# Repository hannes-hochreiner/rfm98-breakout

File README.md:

# rfm98-breakout
Breakout board for the RFM98 LoRa transceiver module.

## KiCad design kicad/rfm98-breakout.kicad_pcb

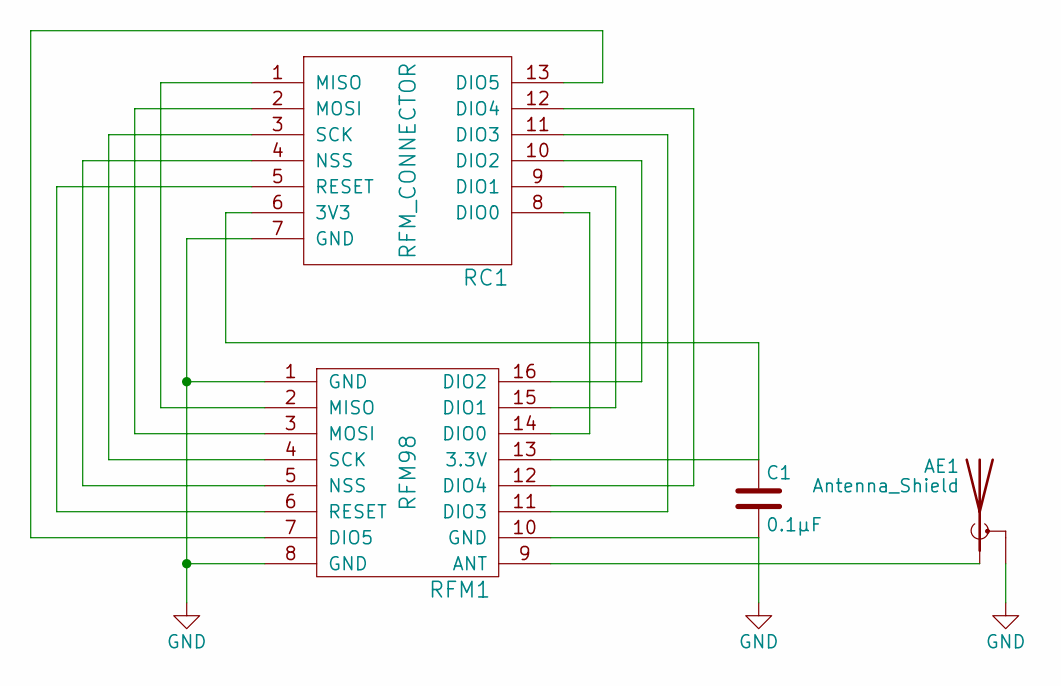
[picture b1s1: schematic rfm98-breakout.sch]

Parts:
AE1: Antenna_Shield; MOLEX-0732511150; Digi-Key Part Number WM5534-ND
C1: 0.1µF; C_0603_HandSoldering
RC1: RFM_CONNECTOR; RFM98_CON
RFM1: RFM98; Digi-Key Part Number 1597-1491-ND

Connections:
GND: AE1.2 (Shield), C1.2, RC1.7 (GND), RFM1.1 (GND), RFM1.8 (GND), RFM1.10 (GND)
unnamed: AE1.1 (A), RFM1.9 (ANT)
unnamed: C1.1, RC1.6 (3V3), RFM1.13 (3.3V)
unnamed: RC1.1 (MISO), RFM1.2 (MISO)
unnamed: RC1.2 (MOSI), RFM1.3 (MOSI)
unnamed: RC1.3 (SCK), RFM1.4 (SCK)
unnamed: RC1.4 (NSS), RFM1.5 (NSS)
unnamed: RC1.5 (RESET), RFM1.6 (RESET)
unnamed: RC1.8 (DIO0), RFM1.14 (DIO0)
unnamed: RC1.9 (DIO1), RFM1.15 (DIO1)
unnamed: RC1.10 (DIO2), RFM1.16 (DIO2)
unnamed: RC1.11 (DIO3), RFM1.11 (DIO3)
unnamed: RC1.12 (DIO4), RFM1.12 (DIO4)
unnamed: RC1.13 (DIO5), RFM1.7 (DIO5)

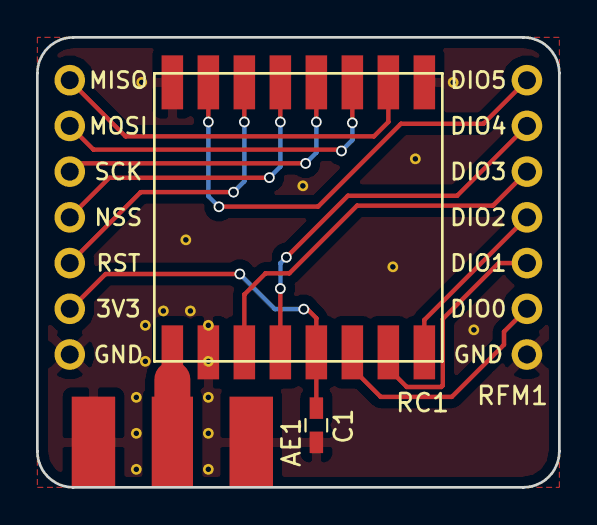
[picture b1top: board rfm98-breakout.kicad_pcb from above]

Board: 2 copper layers, 29.0 x 25.0 mm, 4 parts (0 on the bottom side), 14 nets.

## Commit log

2017-09-16 first version
2017-09-18 rotated rf module
2019-02-12 added a program to control the breakout from a raspberry pi
